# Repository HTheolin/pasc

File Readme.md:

# Användbara länkar

## Rust
svd2rust - https://docs.rs/svd2rust/0.14.0/svd2rust/  \
Rustboken - https://doc.rust-lang.org/1.4.0/book/README.html  \
Embedde rust - https://rust-embedded.github.io/book/intro/index.html  \
CubeMX och Rust - http://www.hashmismatch.net/pragmatic-bare-metal-rust/

## Hårdvara
STM32F401RE datasheet - https://www.st.com/resource/en/datasheet/stm32f401re.pdf

## Dokument
High Level specification - https://docs.google.com/document/d/1pT679ALJbP6M4RAu0LiHIDUVMe5iSUqeqp4-EVYOUyA/edit# \
Komponenter - https://docs.google.com/spreadsheets/d/1eK-V_FMpTHM5hmX8ijiI2q-JYo_6xdile7O38F0DbRs/edit#gid=0

# High Level Specification
Hälsoarmband som mäter puls och steg med pulsmätare och accelerometer.
Knapp som startar och återställer stegräknare. Strömspar som stänger display, sänker sampling frekvens, ... ev. efter lång tid utan knapptryck.
## Purpose (what problem it solves)
Mäta puls och känna av om pulsen blir låg/hög, varna vid dessa.
## Limitations (what problem(s) it cannot solve)
Visar endast realtid puls, yttre temperatur och steg, inget minne. Larmar endast närmaste omgivningen. 
## Behaviour (how the problem is solved)
Genom att mäta puls med en sensor en gång per sek, om den blir låg eller hög starta larm med högtalare. Visar data på display. Återställer data och startar genom knapptryck. Med detta system skapas en tryggare värld.

## Safety (what it must not do, e.g., electrocute the user)
Eftersom systemet är designat att vara i kontakt med person, måste tåla viss mängd fukt och inte ge elektiska stötar till användaren.
## Liveness (what it must eventually do, e.g., process data) 
Måste visa puls minst var 10e sekund under batteritid. 
## Robustness (how it should react to non-expected input, e.g., mal-formed packages)
Om ingen puls stäng system. 

# Gradings
## Grade 3
Pulse measurements from analog in. \
Timer that's set using buttons. \
Buzzer that sounds alarm when high pulse or timer reaching zero. \
USART for serial communication with com.
## Grade 4
Temperature measurements using analog in. \
Output to display using SPI \
Low power mode
## Grade 5
Accelerometer detecting steps, using accelerometer values or tap interrupts over I2C. \
Menu for selecting output to display and other settings.

# Group division
All - STM 32 init, Soldering \
August - ADC, Buttons, Display Layouts \
Simon - USART, Display \
Ridge - Timer, Piezo \
Henrik - Display, Acccelerometer

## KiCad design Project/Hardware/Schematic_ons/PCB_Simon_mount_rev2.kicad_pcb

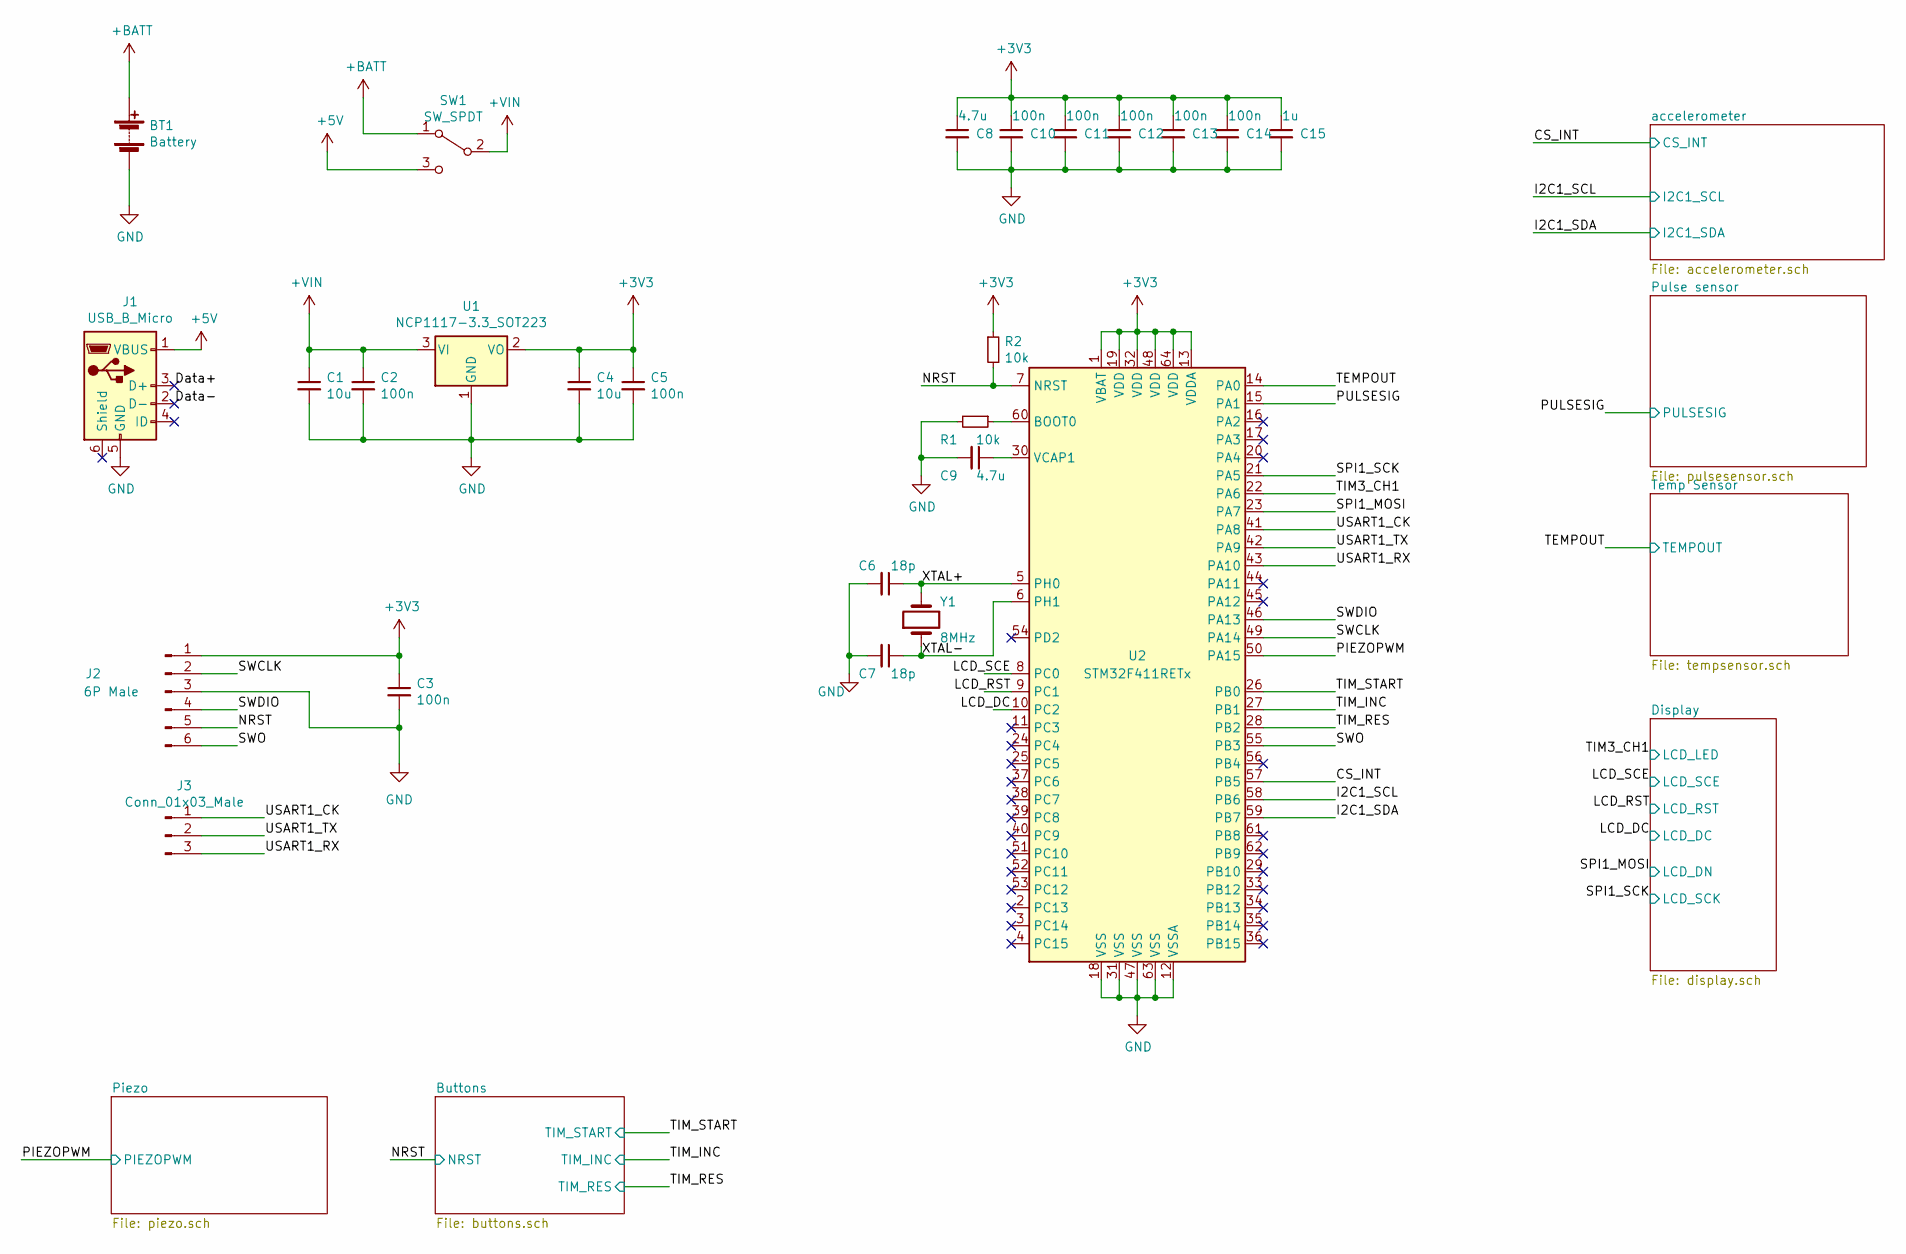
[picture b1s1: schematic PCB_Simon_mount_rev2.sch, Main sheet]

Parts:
BT1: Battery; PinHeader_1x02_P2.54mm_Vertical
C1, C4: 10u; CP_Radial_D5.0mm_P2.00mm
C2, C3, C5, C10, C11, C12, C13, C14: 100n; C_0805_2012Metric_Pad1.15x1.40mm_HandSolder
C6, C7: 18p; C_0805_2012Metric_Pad1.15x1.40mm_HandSolder
C8, C9: 4.7u; C_0805_2012Metric_Pad1.15x1.40mm_HandSolder
C15: 1u; C_0805_2012Metric_Pad1.15x1.40mm_HandSolder
J1: USB_B_Micro; USB_Micro_B_Female_10118193-0001LF
J2: 6P Male; PinHeader_1x06_P2.54mm_Vertical
J3: Conn_01x03_Male; PinHeader_1x03_P2.54mm_Vertical
R1, R2: 10k; R_0805_2012Metric_Pad1.15x1.40mm_HandSolder
SW1: SW_SPDT; SPDT-100
U1: NCP1117-3.3_SOT223; SOT-223-3_TabPin2
U2: STM32F411RETx; LQFP-64_10x10mm_P0.5mm
Y1: 8MHz; Crystal_SMD_HC49-SD_HandSoldering

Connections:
+5V: J1.1 (VBUS), SW1.3 (C)
+BATT: BT1.1 (+), SW1.1 (A)
+VIN: C1.1, C2.1, SW1.2 (B), U1.3 (VI)
/CS_INT: U2.57 (PB5); also elsewhere on the board
/Data+: J1.3 (D+)
/Data-: J1.2 (D-)
/I2C1_SCL: U2.58 (PB6); also elsewhere on the board
/I2C1_SDA: U2.59 (PB7); also elsewhere on the board
/LCD_DC: U2.10 (PC2); also elsewhere on the board
/LCD_RST: U2.9 (PC1); also elsewhere on the board
/LCD_SCE: U2.8 (PC0); also elsewhere on the board
/NRST: J2.5, R2.2, U2.7 (NRST); also elsewhere on the board
/PIEZOPWM: U2.50 (PA15); also elsewhere on the board
/PULSESIG: U2.15 (PA1); also elsewhere on the board
/SPI1_MOSI: U2.23 (PA7); also elsewhere on the board
/SPI1_SCK: U2.21 (PA5); also elsewhere on the board
/SWCLK: J2.2, U2.49 (PA14)
/SWDIO: J2.4, U2.46 (PA13)
/SWO: J2.6, U2.55 (PB3)
/TEMPOUT: U2.14 (PA0); also elsewhere on the board
/TIM3_CH1: U2.22 (PA6); also elsewhere on the board
/TIM_INC: U2.27 (PB1); also elsewhere on the board
/TIM_RES: U2.28 (PB2); also elsewhere on the board
/TIM_START: U2.26 (PB0); also elsewhere on the board
/USART1_CK: J3.1, U2.41 (PA8)
/USART1_RX: J3.3, U2.43 (PA10)
/USART1_TX: J3.2, U2.42 (PA9)
/XTAL+: C6.1, U2.5 (PH0), Y1.2
/XTAL-: C7.1, U2.6 (PH1), Y1.1
GND: BT1.2 (-), C1.2, C2.2, C3.2, C4.2, C5.2, C6.2, C7.2, C8.2, C9.2, C10.2, C11.2, C12.2, C13.2, C14.2, C15.2, J1.5 (GND), J2.3, R1.2, U1.1 (GND), U2.12 (VSSA), U2.18 (VSS), U2.31 (VSS), U2.47 (VSS), U2.63 (VSS); also elsewhere on the board
unnamed: C9.1, U2.30 (VCAP1)
unnamed: R1.1, U2.60 (BOOT0)

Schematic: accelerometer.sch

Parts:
C16: 100n; C_0805_2012Metric_Pad1.15x1.40mm_HandSolder
U3: lis3dh_board; LIS3DH

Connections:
/CS_INT: U3.8 (INT); also elsewhere on the board
/I2C1_SCL: U3.4 (SCL); also elsewhere on the board
/I2C1_SDA: U3.5 (SDA); also elsewhere on the board
GND: C16.2, U3.3 (GND), U3.6 (SDO); also elsewhere on the board

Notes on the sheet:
I2C Address: 0x18
Use I2C.

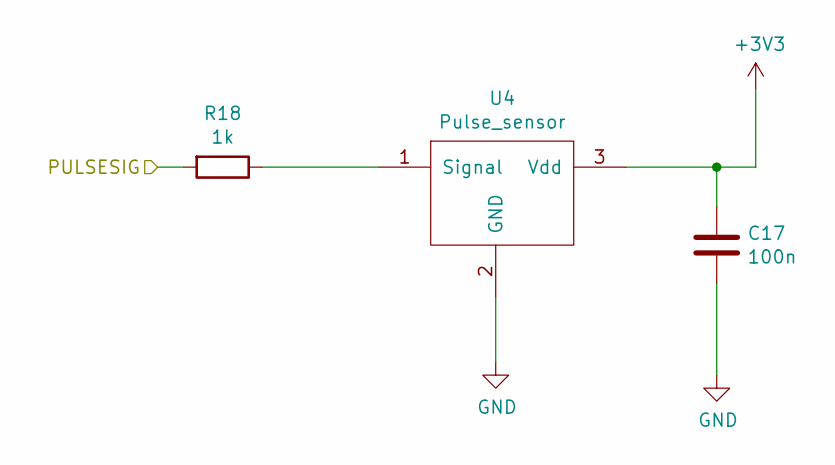
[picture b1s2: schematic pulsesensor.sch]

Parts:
C17: 100n; C_0805_2012Metric_Pad1.15x1.40mm_HandSolder
R18: 1k; R_0805_2012Metric_Pad1.15x1.40mm_HandSolder
U4: Pulse_sensor; PinHeader_1x03_P2.54mm_Vertical

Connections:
/PULSESIG: R18.2; also elsewhere on the board
GND: C17.2, U4.2 (GND); also elsewhere on the board
unnamed: R18.1, U4.1 (Signal)

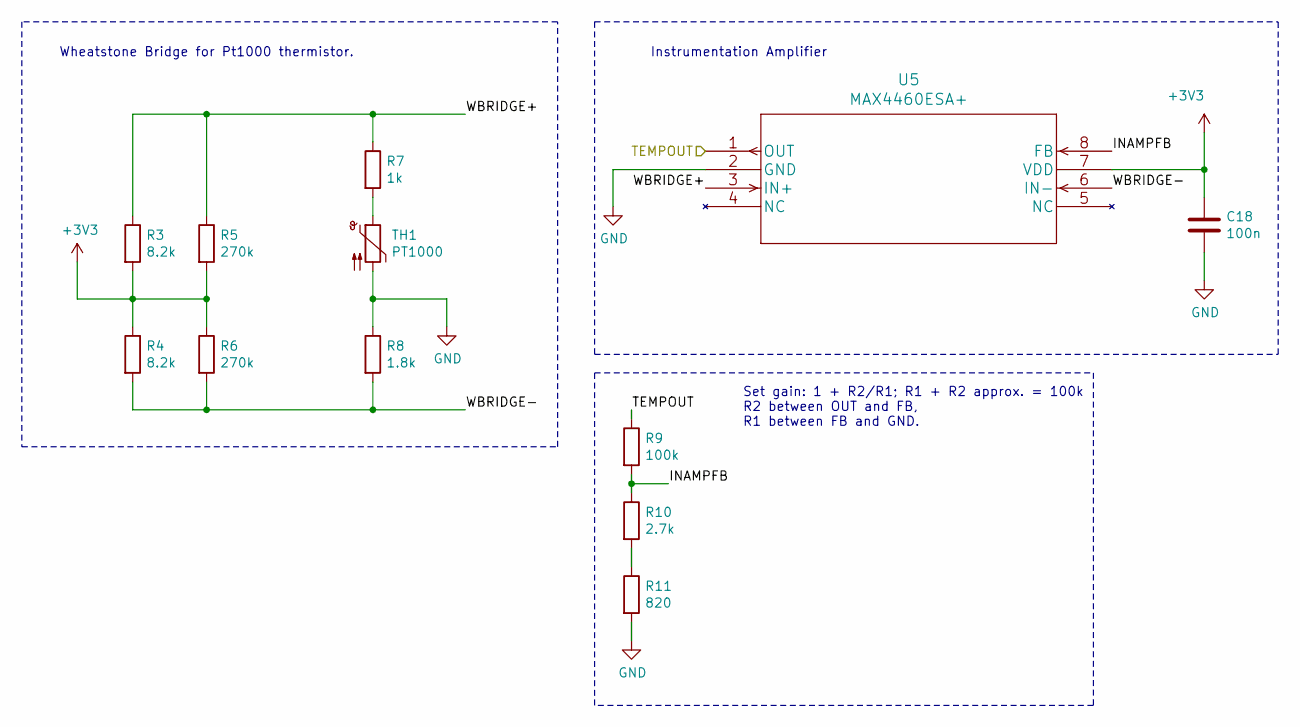
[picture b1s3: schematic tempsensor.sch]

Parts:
C18: 100n; C_0805_2012Metric_Pad1.15x1.40mm_HandSolder
R3, R4: 8.2k; R_0805_2012Metric_Pad1.15x1.40mm_HandSolder
R5, R6: 270k; R_0805_2012Metric_Pad1.15x1.40mm_HandSolder
R7: 1k; R_0805_2012Metric_Pad1.15x1.40mm_HandSolder
R8: 1.8k; R_0805_2012Metric_Pad1.15x1.40mm_HandSolder
R9: 100k; R_0805_2012Metric_Pad1.15x1.40mm_HandSolder
R10: 2.7k; R_0805_2012Metric_Pad1.15x1.40mm_HandSolder
R11: 820; R_0805_2012Metric_Pad1.15x1.40mm_HandSolder
TH1: PT1000; TO-92-2
U5: MAX4460ESA+; SO-8_5.3x6.2mm_P1.27mm

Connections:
/TEMPOUT: R9.1, U5.1 (OUT); also elsewhere on the board
/Temp Sensor/INAMPFB: R9.2, R10.1, U5.8 (FB)
/Temp Sensor/WBRIDGE+: R3.1, R5.1, R7.1, U5.3 (IN+)
/Temp Sensor/WBRIDGE-: R4.2, R6.2, R8.2, U5.6 (IN-)
GND: C18.2, R8.1, R11.2, TH1.2, U5.2 (GND); also elsewhere on the board
unnamed: R7.2, TH1.1
unnamed: R10.2, R11.1

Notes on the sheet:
Set gain: 1 + R2/R1; R1 + R2 approx. = 100k R2 between OUT and FB, R1 between FB and GND.
Instrumentation Amplifier
Wheatstone Bridge for Pt1000 thermistor.

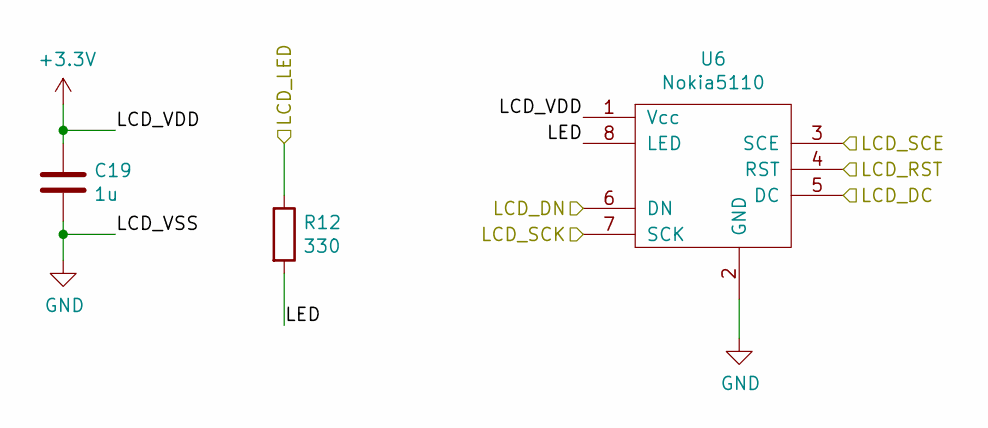
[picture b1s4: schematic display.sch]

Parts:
C19: 1u; C_0805_2012Metric_Pad1.15x1.40mm_HandSolder
R12: 330; R_0805_2012Metric_Pad1.15x1.40mm_HandSolder
U6: Nokia5110

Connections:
/Display/LED: R12.2, U6.8 (LED)
/LCD_DC: U6.5 (DC); also elsewhere on the board
/LCD_RST: U6.4 (RST); also elsewhere on the board
/LCD_SCE: U6.3 (SCE); also elsewhere on the board
/SPI1_MOSI: U6.6 (DN); also elsewhere on the board
/SPI1_SCK: U6.7 (SCK); also elsewhere on the board
/TIM3_CH1: R12.1; also elsewhere on the board
GND: C19.2, U6.2 (GND); also elsewhere on the board

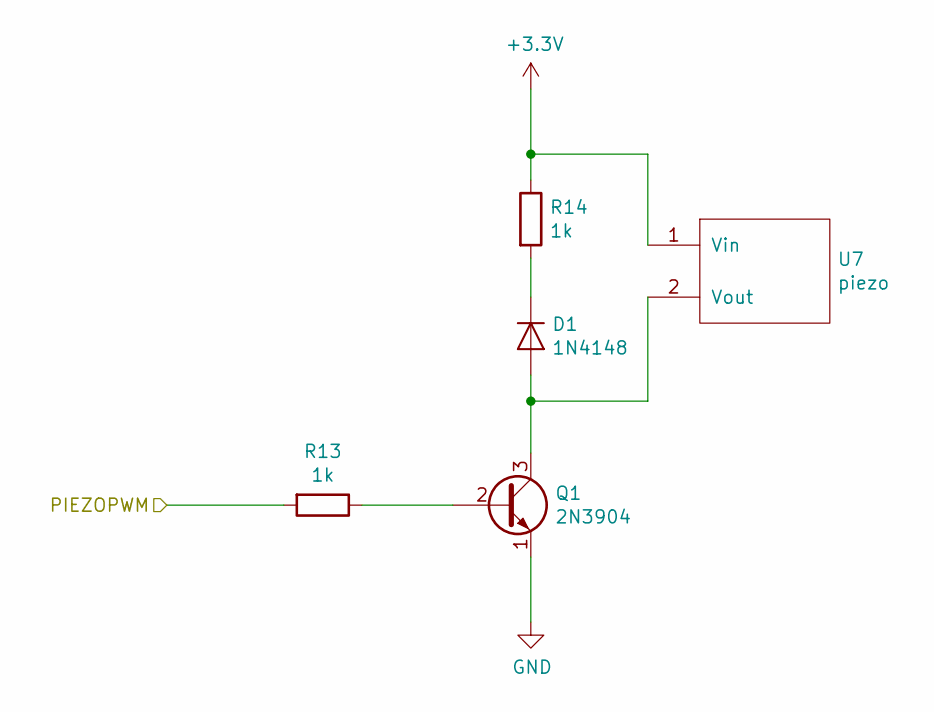
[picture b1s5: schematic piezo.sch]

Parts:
D1: 1N4148; D_DO-35_SOD27_P7.62mm_Horizontal
Q1: 2N3904; TO-92_Inline_Wide
R13, R14: 1k; R_0805_2012Metric_Pad1.15x1.40mm_HandSolder
U7: piezo; Piezo

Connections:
/PIEZOPWM: R13.2; also elsewhere on the board
GND: Q1.1 (E); also elsewhere on the board
unnamed: D1.1 (K), R14.2
unnamed: D1.2 (A), Q1.3 (C), U7.2 (Vout)
unnamed: Q1.2 (B), R13.1

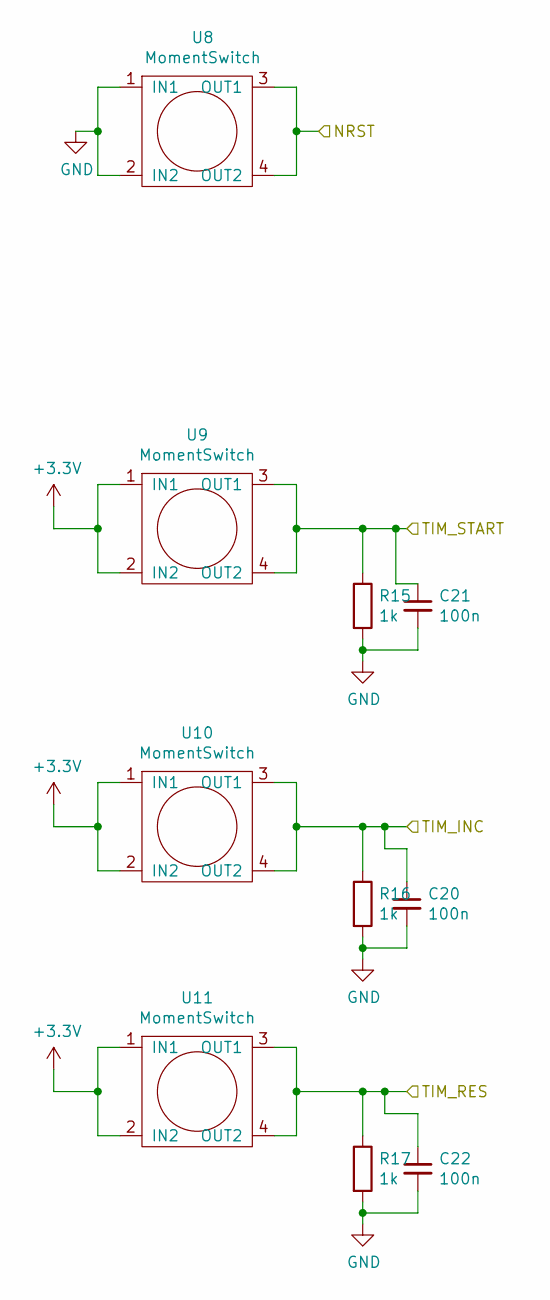
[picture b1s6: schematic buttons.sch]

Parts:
C20, C21, C22: 100n; C_0805_HandSoldering
R15, R16, R17: 1k; R_0805_2012Metric_Pad1.15x1.40mm_HandSolder
U8, U9, U10, U11: MomentSwitch; Momentswitch

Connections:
/NRST: U8.3 (OUT1), U8.4 (OUT2); also elsewhere on the board
/TIM_INC: C20.1, R16.1, U10.3 (OUT1), U10.4 (OUT2); also elsewhere on the board
/TIM_RES: C22.1, R17.1, U11.3 (OUT1), U11.4 (OUT2); also elsewhere on the board
/TIM_START: C21.1, R15.1, U9.3 (OUT1), U9.4 (OUT2); also elsewhere on the board
GND: C20.2, C21.2, C22.2, R15.2, R16.2, R17.2, U8.1 (IN1), U8.2 (IN2); also elsewhere on the board

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
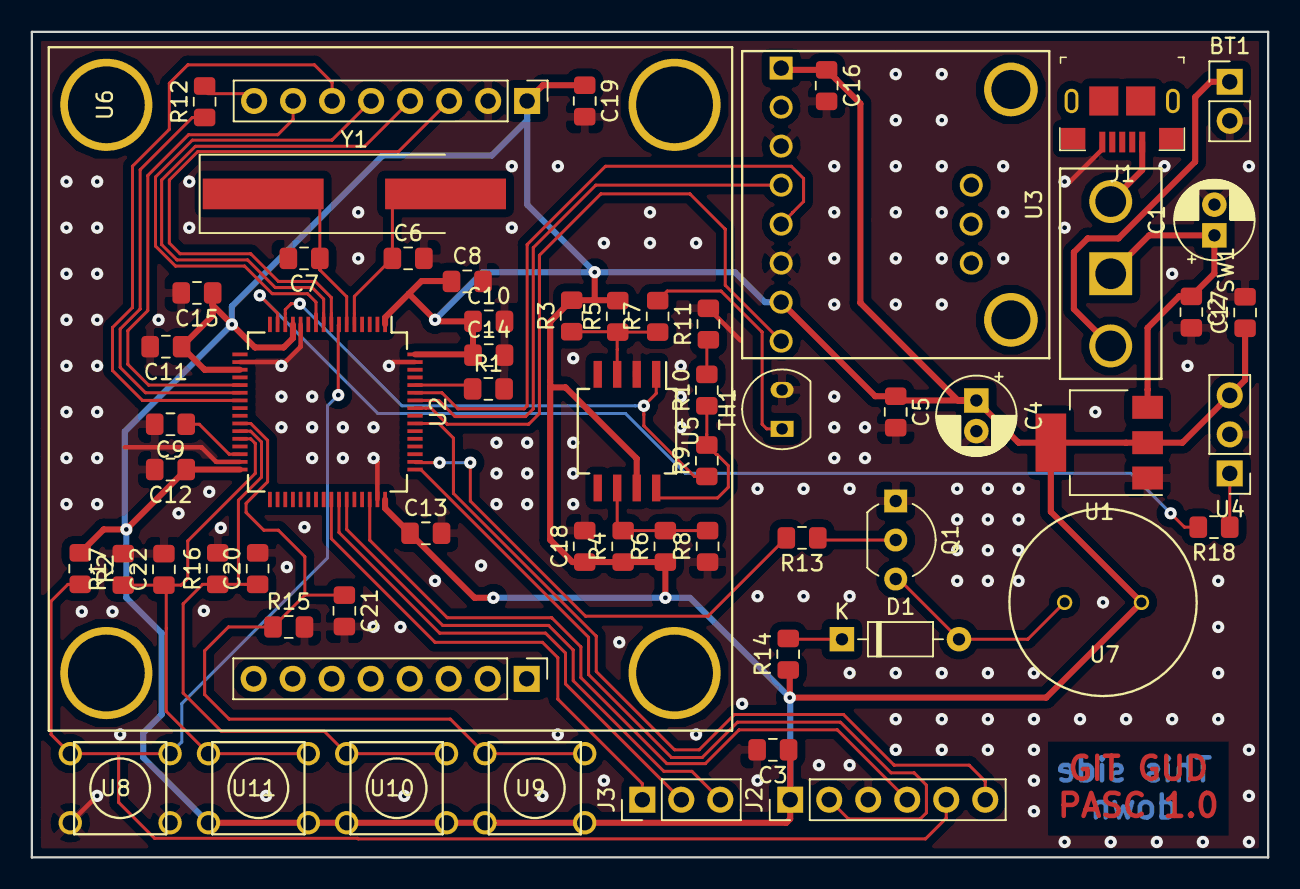
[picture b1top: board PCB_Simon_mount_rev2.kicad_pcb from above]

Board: 2 copper layers, 80.5 x 53.8 mm, 60 parts (0 on the bottom side), 41 nets.

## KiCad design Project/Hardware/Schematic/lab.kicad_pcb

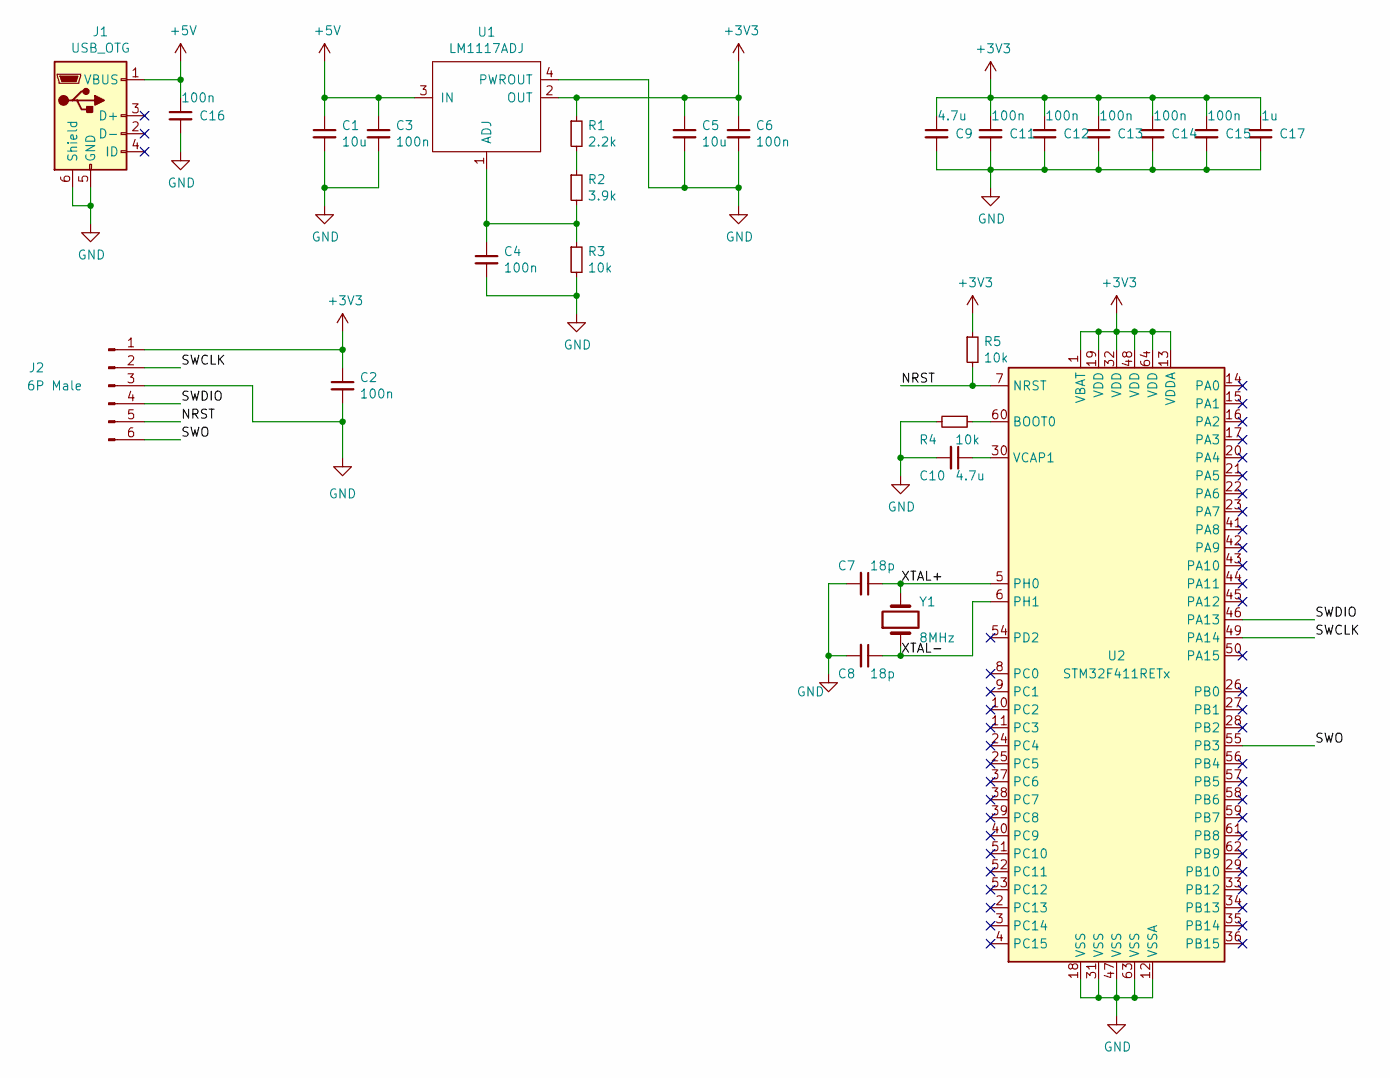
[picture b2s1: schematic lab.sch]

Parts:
C1, C5: 10u; CP_Radial_D5.0mm_P2.00mm
C2, C3, C4, C6, C11, C12, C13, C14, C15, C16: 100n; C_0805_2012Metric_Pad1.15x1.40mm_HandSolder
C7, C8: 18p; C_0805_2012Metric_Pad1.15x1.40mm_HandSolder
C9, C10: 4.7u; C_0805_2012Metric_Pad1.15x1.40mm_HandSolder
C17: 1u; C_0805_2012Metric_Pad1.15x1.40mm_HandSolder
J1: USB_OTG; USB_Mini-B_Lumberg_2486_01_Horizontal
J2: 6P Male; PinHeader_1x06_P2.54mm_Vertical
R1: 2.2k; R_0805_2012Metric_Pad1.15x1.40mm_HandSolder
R2: 3.9k; R_0805_2012Metric_Pad1.15x1.40mm_HandSolder
R3, R4, R5: 10k; R_0805_2012Metric_Pad1.15x1.40mm_HandSolder
U1: LM1117ADJ; SOT-223
U2: STM32F411RETx; LQFP-64_10x10mm_P0.5mm
Y1: 8MHz; Crystal_SMD_HC49-SD_HandSoldering

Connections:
+3V3: C2.1, C5.1, C6.1, C9.1, C11.1, C12.1, C13.1, C14.1, C15.1, C17.1, J2.1, R1.1, R5.1, U1.2 (OUT), U2.1 (VBAT), U2.13 (VDDA), U2.19 (VDD), U2.32 (VDD), U2.48 (VDD), U2.64 (VDD)
+5V: C1.1, C3.1, C16.1, J1.1 (VBUS), U1.3 (IN)
/NRST: J2.5, R5.2, U2.7 (NRST)
/SWCLK: J2.2, U2.49 (PA14)
/SWDIO: J2.4, U2.46 (PA13)
/SWO: J2.6, U2.55 (PB3)
/XTAL+: C7.1, U2.5 (PH0), Y1.2
/XTAL-: C8.1, U2.6 (PH1), Y1.1
GND: C1.2, C2.2, C3.2, C4.2, C5.2, C6.2, C7.2, C8.2, C9.2, C10.2, C11.2, C12.2, C13.2, C14.2, C15.2, C16.2, C17.2, J1.5 (GND), J1.6 (Shield), J2.3, R3.2, R4.2, U1.4 (PWROUT), U2.12 (VSSA), U2.18 (VSS), U2.31 (VSS), U2.47 (VSS), U2.63 (VSS)
unnamed: C4.1, R2.2, R3.1, U1.1 (ADJ)
unnamed: C10.1, U2.30 (VCAP1)
unnamed: R1.2, R2.1
unnamed: R4.1, U2.60 (BOOT0)

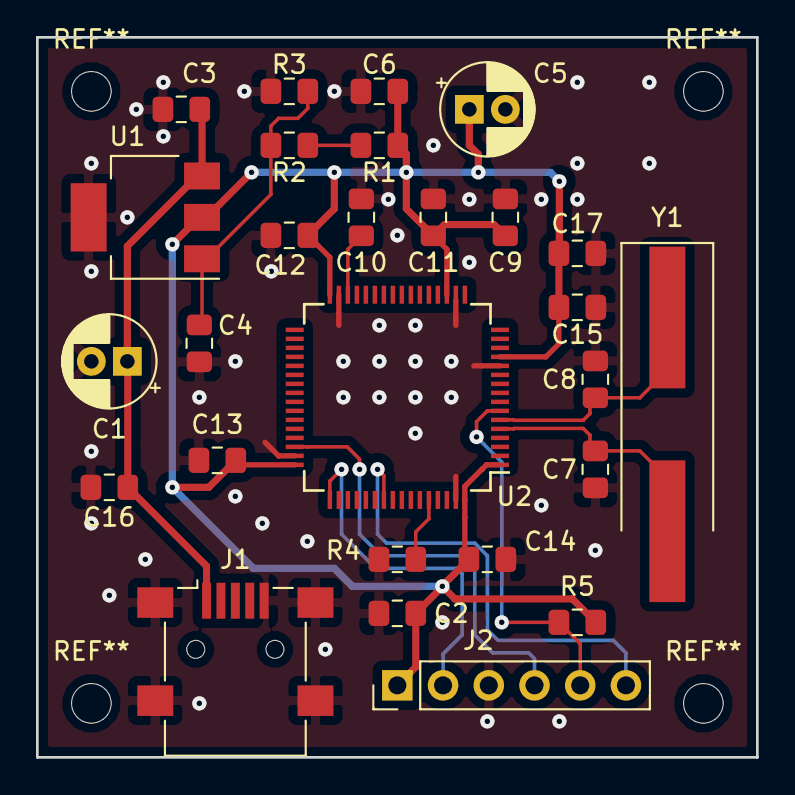
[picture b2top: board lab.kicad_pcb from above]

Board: 2 copper layers, 40.0 x 40.0 mm, 27 parts (0 on the bottom side), 13 nets.

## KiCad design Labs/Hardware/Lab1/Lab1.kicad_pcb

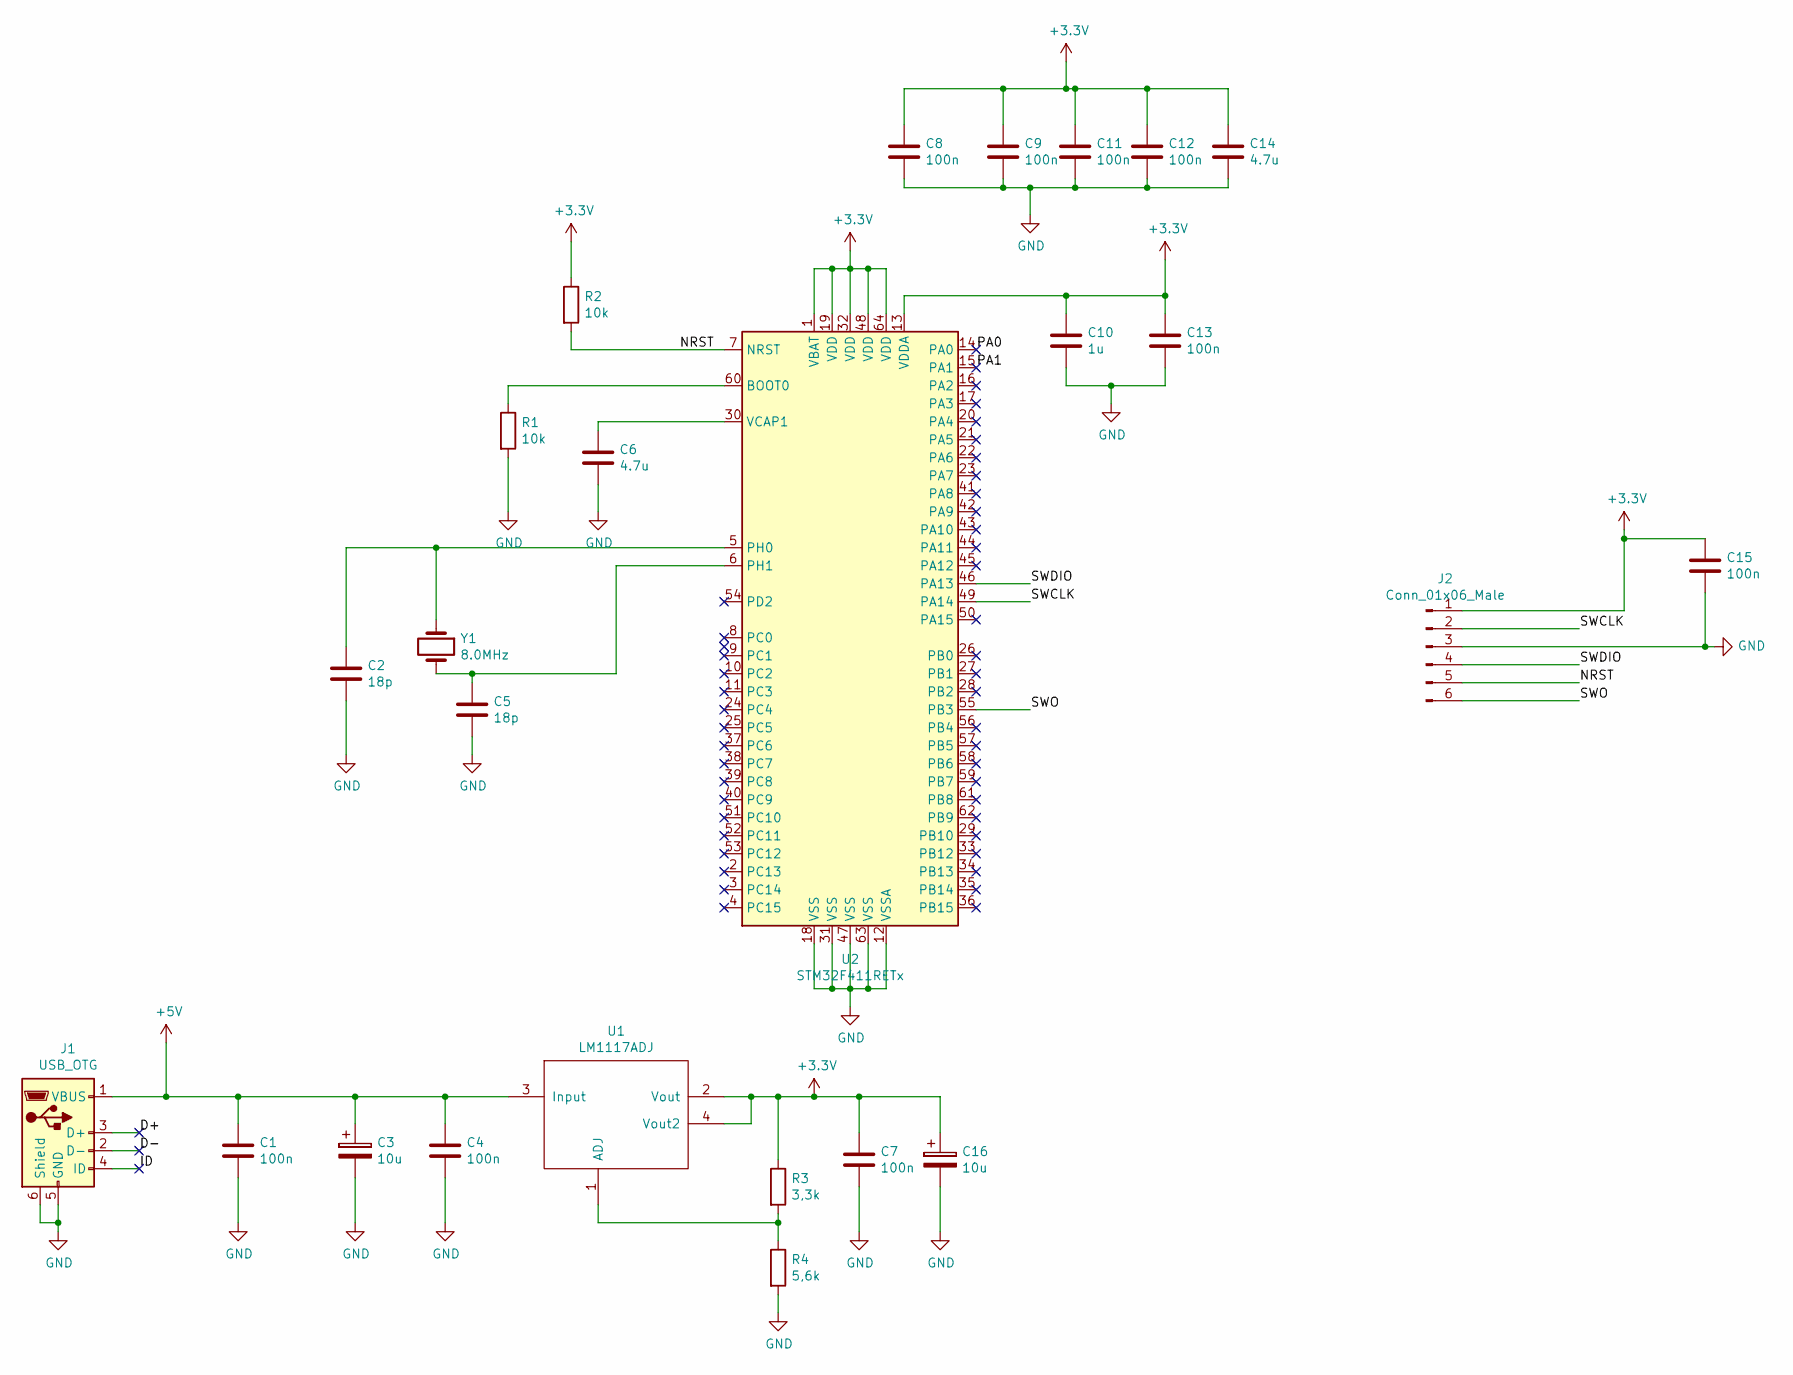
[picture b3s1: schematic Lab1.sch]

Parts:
C1, C4, C7, C8, C9, C11, C12, C13, C15: 100n; C_0805_HandSoldering
C2, C5: 18p; C_0805_HandSoldering
C3, C16: 10u; CP_Elec_5x5.3
C6, C14: 4.7u; C_0805_HandSoldering
C10: 1u; C_0805_HandSoldering
J1: USB_OTG; USB_Mini-B_AdamTech_MUSB-B5-S-VT-TSMT-1_SMD_Vertical
J2: Conn_01x06_Male; Pin_Header_Straight_1x06_Pitch2.54mm_SMD_Pin1Left
R1, R2: 10k; R_0805_HandSoldering
R3: 3,3k; R_0805_HandSoldering
R4: 5,6k; R_0805_HandSoldering
U1: LM1117ADJ; SOT-223
U2: STM32F411RETx; LQFP-64_10x10mm_Pitch0.5mm
Y1: 8.0MHz; Crystal_HC49-U_Vertical

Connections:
+3V3: C7.1, C8.1, C9.1, C10.1, C11.1, C12.1, C13.1, C14.1, C15.1, C16.1, J2.1, R2.1, R3.1, U1.2 (Vout), U1.4 (Vout2), U2.1 (VBAT), U2.13 (VDDA), U2.19 (VDD), U2.32 (VDD), U2.48 (VDD), U2.64 (VDD)
+5V: C1.1, C3.1, C4.1, J1.1 (VBUS), U1.3 (Input)
/D+: J1.3 (D+)
/D-: J1.2 (D-)
/ID: J1.4 (ID)
/NRST: J2.5, R2.2, U2.7 (NRST)
/PA0: U2.14 (PA0)
/PA1: U2.15 (PA1)
/SWCLK: J2.2, U2.49 (PA14)
/SWDIO: J2.4, U2.46 (PA13)
/SWO: J2.6, U2.55 (PB3)
GND: C1.2, C2.2, C3.2, C4.2, C5.2, C6.2, C7.2, C8.2, C9.2, C10.2, C11.2, C12.2, C13.2, C14.2, C15.2, C16.2, J1.5 (GND), J1.6 (Shield), J2.3, R1.2, R4.2, U2.12 (VSSA), U2.18 (VSS), U2.31 (VSS), U2.47 (VSS), U2.63 (VSS)
unnamed: C2.1, U2.5 (PH0), Y1.1
unnamed: C5.1, U2.6 (PH1), Y1.2
unnamed: C6.1, U2.30 (VCAP1)
unnamed: R1.1, U2.60 (BOOT0)
unnamed: R3.2, R4.1, U1.1 (ADJ)

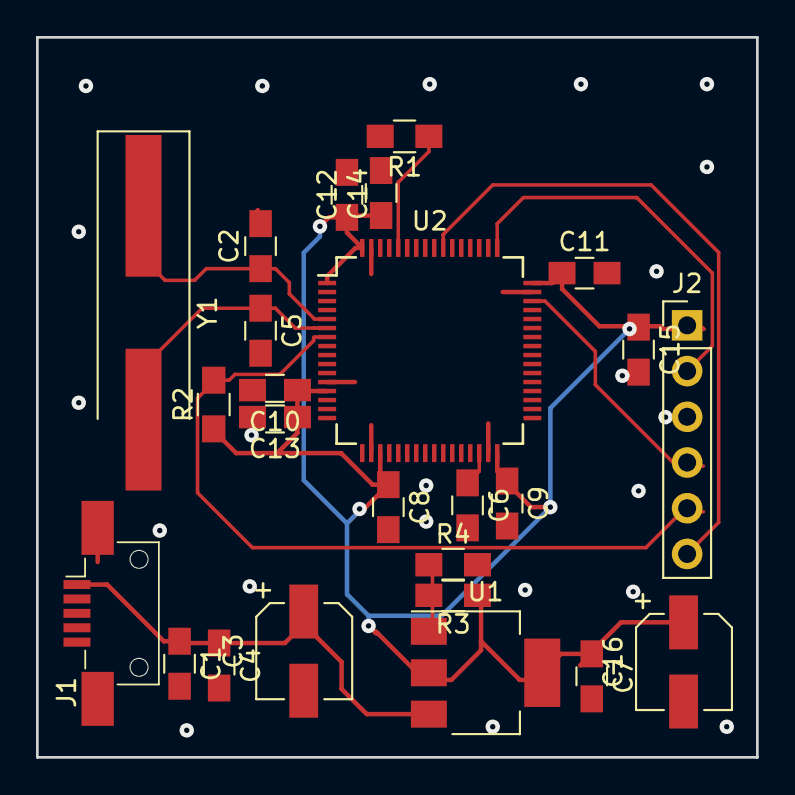
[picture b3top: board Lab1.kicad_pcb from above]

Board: 2 copper layers, 40.0 x 40.0 mm, 25 parts (0 on the bottom side), 12 nets.

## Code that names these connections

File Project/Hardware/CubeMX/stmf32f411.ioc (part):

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Mcu.Name=STM32F411R(C-E)Tx
Mcu.Package=LQFP64
Mcu.UserName=STM32F411RETx
PA0-WKUP.Signal=ADCx_IN0
PA1.Signal=ADCx_IN1
PA10.Mode=Synchronous
PA10.Signal=USART1_RX
PA13.Signal=SYS_JTMS-SWDIO
PA14.Signal=SYS_JTCK-SWCLK
PA15.Signal=S_TIM2_CH1_ETR
PA5.Mode=Simplex_Bidirectional_Master
PA5.Signal=SPI1_SCK
PA6.Signal=S_TIM3_CH1
PA7.Mode=Simplex_Bidirectional_Master
PA7.Signal=SPI1_MOSI
PA8.Mode=Synchronous
PA8.Signal=USART1_CK
PA9.Mode=Synchronous
PA9.Signal=USART1_TX
PB0.Signal=GPIO_Input
PB1.Signal=GPIO_Input
PB2.Signal=GPIO_Input
PB3.Signal=SYS_JTDO-SWO
PB5.Signal=GPXTI5
PB6.Mode=I2C
PB6.Signal=I2C1_SCL
PB7.Mode=I2C
PB7.Signal=I2C1_SDA
PC0.Signal=GPIO_Output
PC1.Signal=GPIO_Output
PC10.Signal=GPIO_Output
PC11.Signal=GPIO_Output
PC2.Signal=GPIO_Output
RCC.HSE_VALUE=25000000
RCC.SYSCLKFreq_VALUE=16000000

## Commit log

2019-01-22 First
2019-01-22 Filstruktur och High level spec
2019-01-22 Fixa formatering
2019-01-22 Lade till användbara länkar
2019-01-22 Linespace i readme
2019-01-22 Lab1 påbörjad
2019-01-29 Lab 1
2019-01-29 Länkar till drive dokument
2019-01-29 Cubemx project
2019-01-30 Lab2 med gerber
2019-01-30 ignore target dir, tagit bort autosave
2019-01-30 Första projekt KiCAD commit.
2019-02-01 sensor ritning
2019-02-01 Accelerometer footprint
2019-02-01 Lagt till sheets för alla delar
2019-02-02 Lade till krets för temperatursensor.
2019-02-02 MATLAB-script för design av temperaturkrets
2019-02-03 Lade till simuleringsplot av temperatursensorkretsen.
2019-02-03 Lade till anteckningar för design av temperatursensorkretsen.
2019-02-04 Lade till komponentvärden i kretsschemat för temperatursensorkretsen
2019-02-04 Lade till display som symbol i KiCAD bibliotek PASC
2019-02-04 Skapade LCD symbol och lade till display-krets.
2019-02-04 Lade till gate-resistor till LCD-backlight FETen.
2019-02-05 Ändrade power supply till två fixed: en 3v3 och en 5v.
2019-02-05 Connections till processor
2019-02-05 Lagt till i2c och usart i cubemx
2019-02-05 lab-cache ändring
2019-02-05 Accelerometer (#1)
    * Accelerometer footprint
    * Connections till processor
    * Lagt till i2c och usart i cubemx
2019-02-05 La till connection stm32 till display, footprint for DEM16220 lcd
2019-02-05 La till connection stm32 till display, footprint for DEM16220 lcd (#4)
2019-02-06 Ändrade i display: lade till LED-kontroll, bytte plats på LED- LED+ utifrån databladet.
2019-02-07 Rätta felstavning
2019-02-07 Ändrade CS-pin på accelerometern, lade till kommentarer och värde på bypassen.
2019-02-07 Add files via upload
    Switches inlagda och MicroUSB
2019-02-08 Add files via upload (#6)
    Switches inlagda och MicroUSB
2019-02-08 Add files via upload
    .lib fil med switch
2019-02-08 Pulse lib
2019-02-08 Fixa bibliotek ref
2019-02-08 Pulse, piezo och labels (#8)
2019-02-08 Pin mappning i cubemx
2019-02-08 Bytte display
2019-02-08 Ny display, igen!
2019-02-08 Lade till symbol för +7V och 7-voltsregulatorn, samt kopplade in regulatorn.
2019-02-08 Korrigerade 7-voltsregulatorn: det är fixed, inte adjustable.
2019-02-08 Buttons och display
2019-02-08 Buttons och display (#9)
2019-02-08 Display footprint
2019-02-08 Display fix
2019-02-08 La till en till display och fixa fel
2019-02-08 Lcd (#10)
    * La till en till display och fixa fel
2019-02-12 Byta skämr, igen igen
2019-02-12 Byta skärm, igen igen (#11)
2019-02-12 La till pins till cubemx, bytte transistor till piezo och la till footprint för accelerometer
2019-02-12 Tog bort power supply +7, lade till switch för att switcha mellan batteri och USB power. Lade till power-net symbol för oregulerad supply voltage +VIN.
2019-02-12 Tagit bort knapp, ändrat power till piezo
2019-02-12 Lcd bb (#12)
    * Tagit bort knapp, ändrat power till piezo
2019-02-12 Intermediate...
2019-02-12 Netlist genererad for ubuntu libs
2019-02-12 Justerade accelerometern lite. Satte ut mått, att ha en platt grej bekvämt på underarmen kräver att den är högst kanske 5 cm bred.
2019-02-12 Missade några filer förra commiten
2019-02-13 Add files via upload
    Klar PCB av Simon
2019-02-13 Lade till vippströmställare footprint och uppdaterade max4460 footprint för att det förhoppningsvis ska laddas av alla
2019-02-13 Rev 2 pcb
2019-02-13 Pcb rev 3
2019-02-13 Pcb rev 4
2019-02-13 Tog bort oanvända filer
2019-02-13 Add files via upload
    Remake nummer dos
2019-02-15 Extra resistor till temp gain, två cubemx project med olika pinsmaps, Gerber filer till pcb_revS
2019-02-15 Updatera footprint för Switch samt gerber
2019-02-15 Pcb rev1 (#13)
    * Extra resistor till temp gain, två cubemx project med olika pinsmaps, Gerber filer till pcb_revS
    * Updatera footprint för Switch samt gerber
2019-02-15 High level design grafik
2019-02-15 Gerber, csv boom, cap till knappar
2019-02-15 Lade till display CAD fil.
2019-02-15 Add files via upload
    Added resistor to pulse, and capacitors to buttons
2019-02-15 Pcb rev1 simon (#14)
    Klar PCB av Simon
    Added resistor to pulse, and capacitors to buttons
2019-02-15 Updaterat footprint samt boom
2019-02-15 Hardware finished for ordering
2019-03-05 First commit for software
2019-03-06 ITM works.
2019-03-08 Started work on ADC, shamlessly implemented from https://github.com/jsjolund/f4/blob/master/src/adc.rs
2019-03-10 Pwm påbörjad
2019-03-10 Tog bort oanvänd crate och onödiga unsafe
2019-03-12 none
2019-03-12 Pwm (#15)
    dma.rs för buffer som kan ändra duty varje period, frequency.rs för att hantera Time typ som kan förstås av f4, time.rs tidsenheter Hz, sec mm, pwm.rs implementerar PWM för 4 timers med 4 olika kanal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
2019-03-12 ADC för adc1 in0 och in1
2019-03-12 Added for more timer imp on ADC
2019-03-12 Added interrupt for DMA2_stream0 to read adc conversions
2019-03-12 Adc (#16)
    * ADC för adc1 in0 och in1
    * Added for more timer imp on ADC
    * Added interrupt for DMA2_stream0 to read adc conversions
2019-03-13 Buttons
2019-03-13 Added both board pin layouts for buttons
2019-03-13 started with lcd crate
2019-03-14 Display init and demo, untested
2019-03-14 Spi (#17)
    * Display init and demo, untested
2019-03-17 Ändrat buttons så att den tar referens, kanske lagat pcd8544 strukt
2019-03-18 Added splash screen from LCD crate
2019-03-18 Spi (#18)
    * Ändrat buttons så att den tar referens, lagat pcd8544 struct
    * Added splash screen from LCD crate
2019-03-18 A mess of i2c
2019-03-19 Working on not working i2c
2019-03-19 Simplified toggle between boards, some cleanups
2019-03-19 I2c (#19)
    * A mess of i2c
    * Working on not working i2c
    * Simplified toggle between boards, some cleanups
2019-03-20 Lade till PCBskillnader i readme och lade till LCD-datablad.
2019-03-20 LCD on Simon's PCB (SPCB) requires higher contrast than Henrik's PCB (HPCB)
2019-03-21 Uppdaterade datablad-mappen
2019-03-21 Började med LCD-data struct och implementerade ADC-till-Celsius module
2019-03-22 I Am 51!
2019-03-22 Reading acc values from i2c working
2019-03-22 Fixed values for g-force on axis, added tap interruptthat wont work for detecting steps, maybe freefall detection will
2019-03-22 Increase clock speed
2019-03-22 LCD uppdatering.
2019-03-23 LCD uppdatering: formattering, display-refresh, ...
2019-03-23 I2c (#20)
    * Reading acc values from i2c working
    * Fixed values for g-force on axis, added tap interrupt that wont work for detecting steps, maybe freefall detection will
2019-03-23 Accelerometer struct
2019-03-23 Kinda working pedometer
2019-03-23 Blankline
2019-03-23 Added comments
2019-03-23 Blank
2019-03-23 Accelerometer and Pedometer (#21)
    * Accelerometer struct
    * Kinda working pedometer
2019-03-24 fix accelerometer h l byte order, added sample arrays for max/min values
2019-03-25 Fix gravity values
2019-03-25 Added vector pointing down
2019-03-25 Increased acc sensitivity
2019-03-25 Added pin interrupt check
2019-03-25 Experiment with pedometer from android
2019-03-25 Cleanup
2019-03-26 Pulse sensor.
2019-03-26 Pulse datasheets
2019-03-26 another step detector
2019-03-26 Pedo cont (#22)
    * fix accelerometer h l byte order, added sample arrays for max/min values
    * Fix gravity values
    * Added vector pointing down
    * Increased acc sensitivity
    * Added pin interrupt check
    * Experiment with pedometer from android
2019-03-26 USART added
2019-03-26 Added another step
2019-03-26 Rising edge on buttons 7-9
2019-03-26 Timer things
2019-03-26 Working on Pulse counting in Pulse Meter
2019-03-26 optimized lcd clear, filtered step counter
2019-03-27 Pedometer with global world z and velocity estimate
2019-03-27 ultamate pedometer
2019-03-27 Pulse sensor fixed, ADC samples at double freq
2019-03-27 Somewhat cleaner
2019-03-27 Pedo filtered (#23)
    * fix accelerometer h l byte order, added sample arrays for max/min values
    * Fix gravity values
    * Added vector pointing down
    * Increased acc sensitivity
    * Added pin interrupt check
    * Experiment with pedometer from android
2019-03-27 Swap board
2019-03-27 Added guiding for users when bad pulse data
2019-03-27 uart branch
2019-03-27 img arrays
2019-03-27 Redraw heart on toggle
2019-03-27 Pcb h (#24)
    * Added guiding for users when bad pulse data
    * img arrays
    * Redraw heart on toggle
2019-03-27 Setup for board rev_H
2019-03-27 Fix float
2019-03-28 uart without loop
2019-03-28 uart without ends
2019-03-28 Simon usart (#25)
    * uart branch
    * uart without loop
    * uart without ends
